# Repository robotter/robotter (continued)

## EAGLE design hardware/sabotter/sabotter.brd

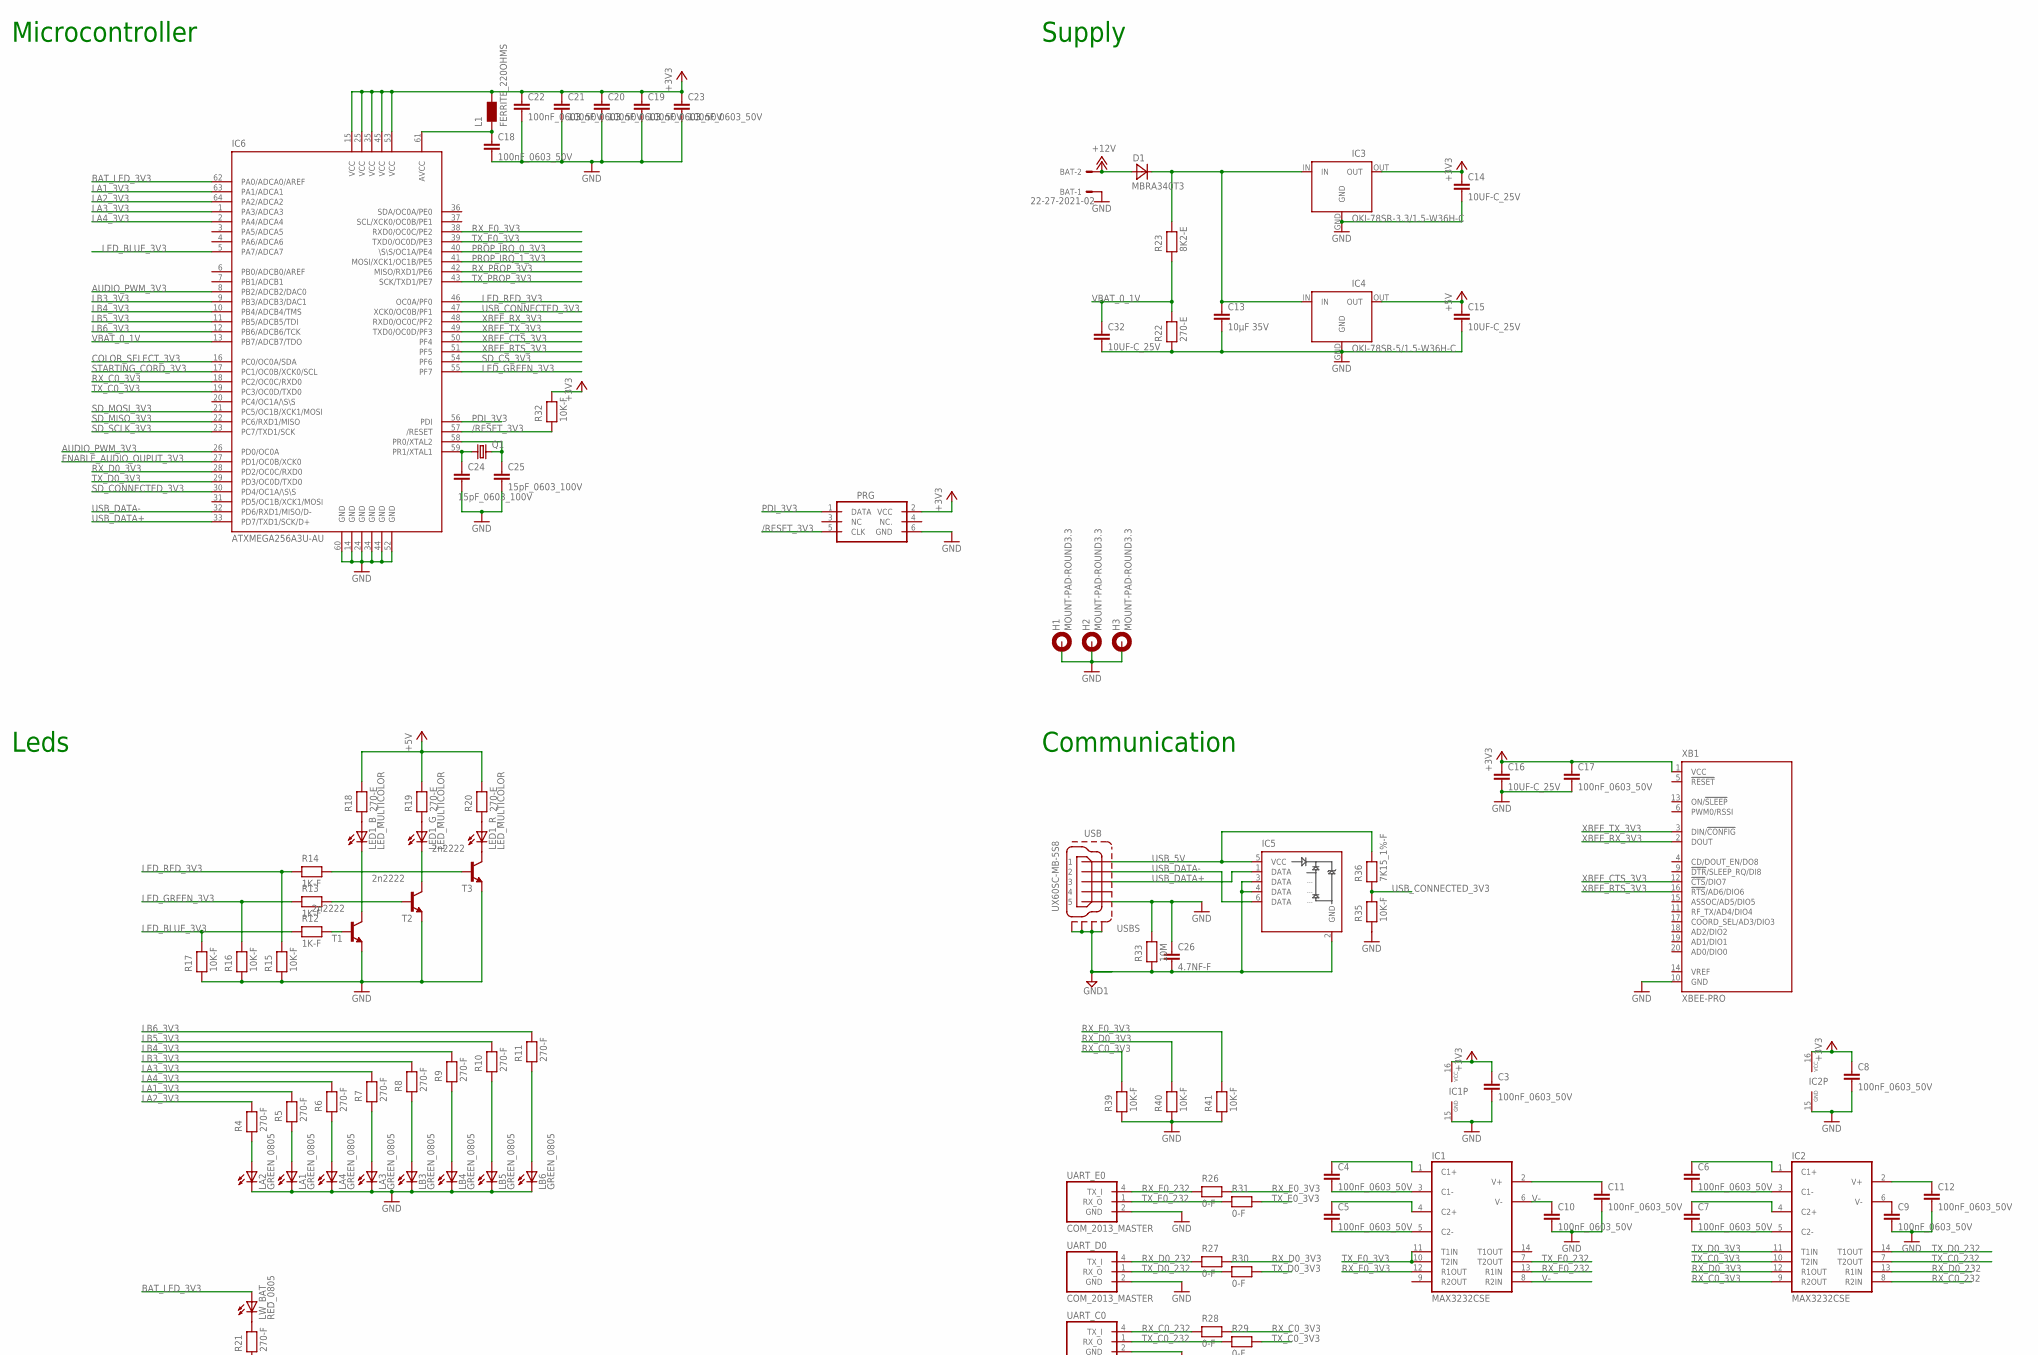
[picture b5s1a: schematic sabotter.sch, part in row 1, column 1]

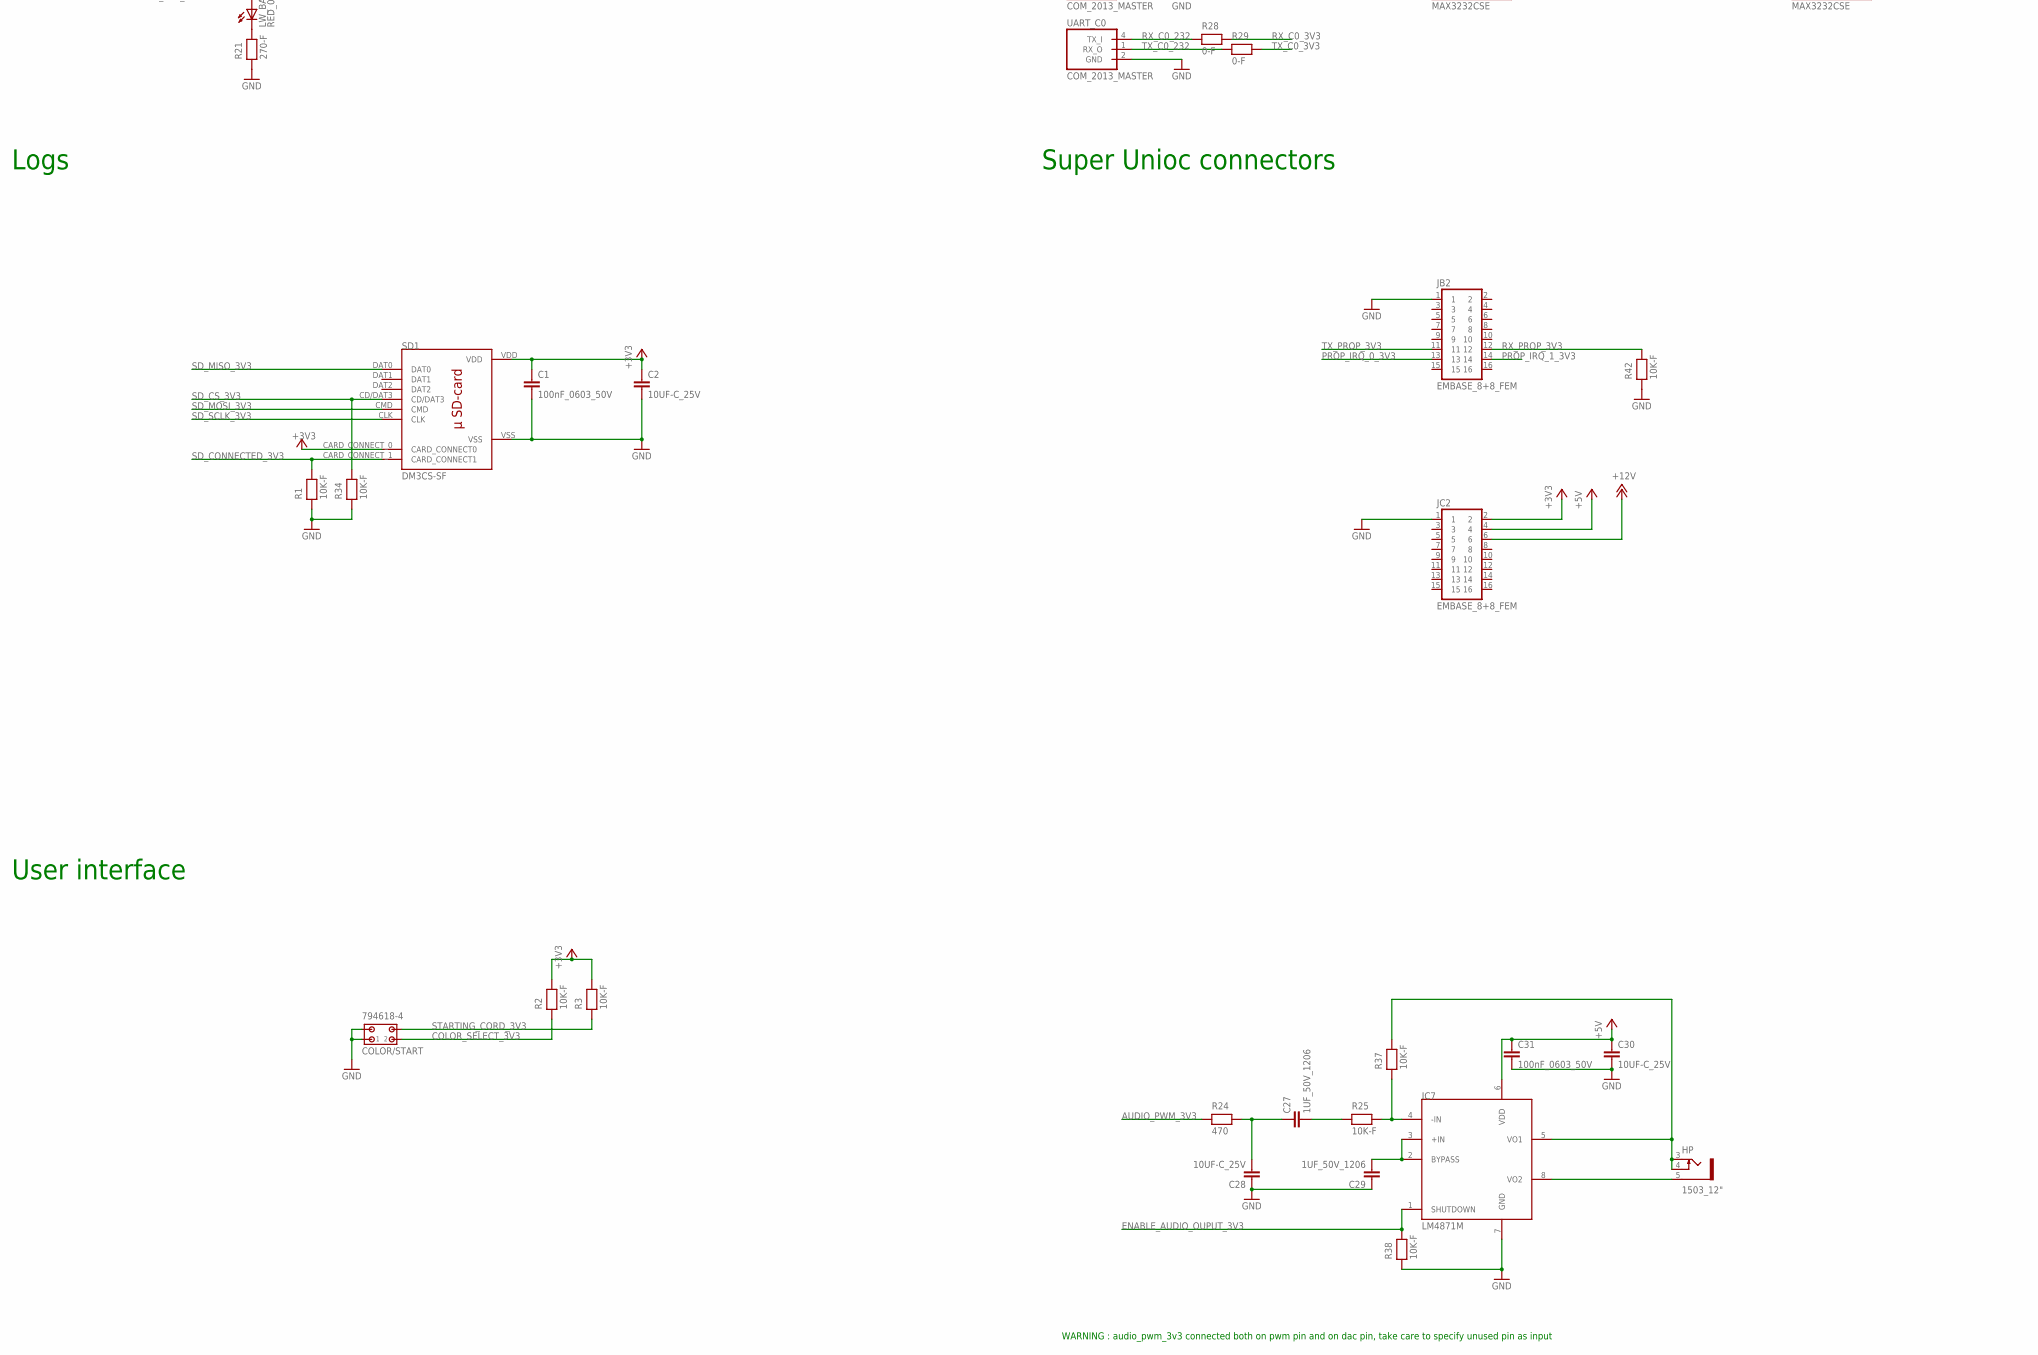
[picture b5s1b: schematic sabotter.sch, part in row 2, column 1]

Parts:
BAT: 22-27-2021-02; 6410-02
C1, C3, C4, C5, C6, C7, C8, C9, C10, C11, C12, C17, C18, C19, C20, C21, C22, C23, C31: 100nF_0603_50V; C0603
C2, C14, C15, C16, C28, C30, C32: 10UF-C_25V; C1210
C13: 10µF 35V; C1210
C24, C25: 15pF_0603_100V; C0603
C26: 4.7NF-F; C0603
C27, C29: 1UF_50V_1206; C1206
COLOR/START: 794618-4
D1: MBRA340T3; SMA
H1, H2, H3: MOUNT-PAD-ROUND3.3; 3,3-PAD
HP: 1503_12"; 1503_12
IC1, IC2: MAX3232CSE; SO16
IC3: OKI-78SR-3.3/1.5-W36H-C; OKI78SR-HORIZONTAL
IC4: OKI-78SR-5/1.5-W36H-C; OKI78SR-HORIZONTAL
IC5: LXES2SBAA4-016; LXES2BAA4
IC6: ATXMEGA256A3U-AU; TQFP64
IC7: LM4871M; SO8
JB2: EMBASE_8+8_FEM
JC2: EMBASE_8+8_FEM
L1: FERRITE_220OHMS; R0603
LA1, LA2, LA3, LA4: GREEN_0805; CHIP-LED0805
LB3, LB4, LB5, LB6: GREEN_0805; CHIP-LED0805
LED1: LED_MULTICOLOR; PLCC6
LW_BAT: RED_0805; CHIP-LED0805
PRG: PDI_ATMELL; ML6L
Q1: CRYSTAL_16MHZ_HC49UP; HC49UP
R1, R2, R3, R15, R16, R17, R25, R32, R34, R35, R37, R38, R39, R40, R41, R42: 10K-F; R0603
R4, R5, R6, R7, R8, R9, R10, R11, R21: 270-F; R0603
R12, R13, R14: 1K-F; R0603
R18, R19, R20, R22: 270-E; R0805
R23: 8K2-E; R0805
R24: 470; R0603
R26, R27, R28, R29, R30, R31: 0-F; R0603
R33: 10M; R0603
R36: 7K15_1%-F; R0603
SD1: DM3CS-SF
T1, T2, T3: 2n2222; SOT23-BEC
UART_C0: COM_2013_MASTER; MICROMATCH-4_SMD
UART_D0: COM_2013_MASTER; MICROMATCH-4_SMD
UART_E0: COM_2013_MASTER; MICROMATCH-4_SMD
USB: UX60SC-MB-5S8; UX60-MB-5S8
XB1: XBEE-PRO

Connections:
+3V3: C1.1, C2.1, C3.1, C8.1, C14.1, C16.1, C17.1, C19.1, C20.1, C21.1, C22.1, C23.1, IC1.16 (VCC), IC2.16 (VCC), IC3.OUT, IC6.15 (VCC), IC6.25 (VCC), IC6.35 (VCC), IC6.45 (VCC), IC6.53 (VCC), JC2.2, L1.2, PRG.2 (VCC), R2.2, R3.2, R32.2, SD1.CARD_CONNECT_0 (CARD_CONNECT0), SD1.VDD, XB1.1 (VCC)
+5V: C15.1, C30.1, C31.1, IC4.OUT, IC7.6 (VDD), JC2.4, R18.2, R19.2, R20.2
+12V: BAT.2, D1.A, JC2.6
/RESET_3V3: IC6.57 (/RESET), PRG.5 (CLK), R32.1
AUDIO_PWM_3V3: IC6.8 (PB2/ADCB2/DAC0), IC6.26 (PD0/OC0A), R24.1
BAT_LED_3V3: IC6.62 (PA0/ADCA0/AREF), LW_BAT.A
COLOR_SELECT_3V3: COLOR/START.2, IC6.16 (PC0/OC0A/SDA), R2.1
ENABLE_AUDIO_OUPUT_3V3: IC6.27 (PD1/OC0B/XCK0), IC7.1 (SHUTDOWN), R38.2
GND: BAT.1, C1.2, C2.2, C3.2, C8.2, C9.2, C10.2, C11.2, C12.2, C13.2, C14.2, C15.2, C16.2, C17.2, C18.2, C19.2, C20.2, C21.2, C22.2, C23.2, C24.2, C25.2, C26.1, C28.1, C29.1, C30.2, C31.2, C32.2, COLOR/START.1, COLOR/START.3, H1.B3,3, H2.B3,3, H3.B3,3, IC1.15 (GND), IC2.15 (GND), IC3.GND, IC4.GND, IC6.14 (GND), IC6.24 (GND), IC6.34 (GND), IC6.44 (GND), IC6.52 (GND), IC6.60 (GND), IC7.7 (GND), JB2.1, JC2.1, LA1.C, LA2.C, LA3.C, LA4.C, LB3.C, LB4.C, LB5.C, LB6.C, PRG.6 (GND), R1.1, R15.1, R16.1, R17.1, R21.1, R22.1, R33.2, R34.1, R35.1, R38.1, R39.1, R40.1, R41.1, R42.1, SD1.VSS, T1.E, T2.E, T3.E, UART_C0.2 (GND), UART_D0.2 (GND), UART_E0.2 (GND), USB.5, XB1.10 (GND)
GND1: C26.2, IC5.2 (GND), IC5.3 (DATA), IC5.4 (DATA), R33.1, USB.M1 (S1), USB.M2 (S2), USB.M3 (S3), USB.M4 (S4)
LA1_3V3: IC6.63 (PA1/ADCA1), R5.2
LA2_3V3: IC6.64 (PA2/ADCA2), R4.2
LA3_3V3: IC6.1 (PA3/ADCA3), R7.2
LA4_3V3: IC6.2 (PA4/ADCA4), R6.2
LB3_3V3: IC6.9 (PB3/ADCB3/DAC1), R8.2
LB4_3V3: IC6.10 (PB4/ADCB4/TMS), R9.2
LB5_3V3: IC6.11 (PB5/ADCB5/TDI), R10.2
LB6_3V3: IC6.12 (PB6/ADCB6/TCK), R11.2
LED_BLUE_3V3: IC6.5 (PA7/ADCA7), R12.1, R17.2
LED_GREEN_3V3: IC6.55 (PF7), R13.1, R16.2
LED_RED_3V3: IC6.46 (OC0A/PF0), R14.1, R15.2
unnamed: LA2.A, R4.1
unnamed: LA1.A, R5.1
unnamed: LB3.A, R8.1
unnamed: LA3.A, R7.1
unnamed: LB4.A, R9.1
unnamed: LB5.A, R10.1
unnamed: LB6.A, R11.1
unnamed: LA4.A, R6.1
unnamed: HP.5, IC7.8 (VO2)
unnamed: C29.2, IC7.2 (BYPASS), IC7.3 (+IN)
unnamed: C9.1, IC2.6 (V-)
unnamed: C27.1, C28.2, R24.2
unnamed: LED1.3 (C), T3.C
unnamed: LED1.2 (C), T2.C
unnamed: LED1.1 (C), T1.C
unnamed: C12.1, IC2.2 (V+)
unnamed: C11.1, IC1.2 (V+)
unnamed: R14.2, T3.B
unnamed: C4.1, IC1.1 (C1+)
unnamed: C6.1, IC2.1 (C1+)
unnamed: C5.1, IC1.4 (C2+)
unnamed: C5.2, IC1.5 (C2-)
unnamed: C4.2, IC1.3 (C1-)
unnamed: C6.2, IC2.3 (C1-)
unnamed: C7.1, IC2.4 (C2+)
unnamed: C7.2, IC2.5 (C2-)
unnamed: C27.2, R25.1
unnamed: IC7.4 (-IN), R25.2, R37.1
unnamed: HP.3, HP.4, IC7.5 (VO1), R37.2
unnamed: R13.2, T2.B
unnamed: R12.2, T1.B
unnamed: LED1.6 (A), R18.1
unnamed: LED1.5 (A), R19.1
unnamed: LED1.4 (A), R20.1
unnamed: LW_BAT.C, R21.2
unnamed: C13.1, D1.C, IC3.IN, IC4.IN, R23.2
unnamed: C18.1, IC6.61 (AVCC), L1.1
unnamed: C24.1, IC6.59 (PR1/XTAL1), Q1.1
unnamed: C25.1, IC6.58 (PR0/XTAL2), Q1.2
PDI_3V3: IC6.56 (PDI), PRG.1 (DATA)
PROP_IRQ_0_3V3: IC6.40 (\S\S/OC1A/PE4), JB2.13
PROP_IRQ_1_3V3: IC6.41 (MOSI/XCK1/OC1B/PE5), JB2.14
RX_C0_3V3: IC2.9 (R2OUT), IC6.18 (PC2/OC0C/RXD0), R28.2, R39.2
RX_C0_232: IC2.8 (R2IN), R28.1, UART_C0.4 (TX_I)
RX_D0_3V3: IC2.12 (R1OUT), IC6.28 (PD2/OC0C/RXD0), R27.2, R40.2
RX_D0_232: IC2.13 (R1IN), R27.1, UART_D0.4 (TX_I)
RX_E0_3V3: IC1.12 (R1OUT), IC6.38 (RXD0/OC0C/PE2), R26.2, R41.2
RX_E0_232: IC1.13 (R1IN), R26.1, UART_E0.4 (TX_I)
RX_PROP_3V3: IC6.42 (MISO/RXD1/PE6), JB2.12, R42.2
SD_CONNECTED_3V3: IC6.30 (PD4/OC1A/\S\S), R1.2, SD1.CARD_CONNECT_1 (CARD_CONNECT1)
SD_CS_3V3: IC6.54 (PF6), R34.2, SD1.CD/DAT3
SD_MISO_3V3: IC6.22 (PC6/RXD1/MISO), SD1.DAT0
SD_MOSI_3V3: IC6.21 (PC5/OC1B/XCK1/MOSI), SD1.CMD
SD_SCLK_3V3: IC6.23 (PC7/TXD1/SCK), SD1.CLK
STARTING_CORD_3V3: COLOR/START.4, IC6.17 (PC1/OC0B/XCK0/SCL), R3.1
TX_C0_3V3: IC2.10 (T2IN), IC6.19 (PC3/OC0D/TXD0), R29.2
TX_C0_232: IC2.7 (T2OUT), R29.1, UART_C0.1 (RX_O)
TX_D0_3V3: IC2.11 (T1IN), IC6.29 (PD3/OC0D/TXD0), R30.2
TX_D0_232: IC2.14 (T1OUT), R30.1, UART_D0.1 (RX_O)
TX_E0_3V3: IC1.10 (T2IN), IC1.11 (T1IN), IC6.39 (TXD0/OC0D/PE3), R31.2
TX_E0_232: IC1.7 (T2OUT), R31.1, UART_E0.1 (RX_O)
TX_PROP_3V3: IC6.43 (SCK/TXD1/PE7), JB2.11
USB_5V: IC5.5 (VCC), R36.2, USB.1
USB_CONNECTED_3V3: IC6.47 (XCK0/OC0B/PF1), R35.2, R36.1
USB_DATA+: IC5.1 (DATA), IC6.33 (PD7/TXD1/SCK/D+), USB.3
USB_DATA-: IC5.6 (DATA), IC6.32 (PD6/RXD1/MISO/D-), USB.2
V-: C10.1, IC1.6 (V-), IC1.8 (R2IN)
VBAT_0_1V: C32.1, IC6.13 (PB7/ADCB7/TDO), R22.2, R23.1
XBEE_CTS_3V3: IC6.50 (PF4), XB1.12 (!CTS!/DIO7)
XBEE_RTS_3V3: IC6.51 (PF5), XB1.16 (!RTS!/AD6/DIO6)
XBEE_RX_3V3: IC6.48 (RXD0/OC0C/PF2), XB1.2 (DOUT)
XBEE_TX_3V3: IC6.49 (TXD0/OC0D/PF3), XB1.3 (DIN/!CONFIG)

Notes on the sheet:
Microcontroller
Supply
Leds
Communication
Logs
Super Unioc connectors
User interface
WARNING : audio_pwm_3v3 connected both on pwm pin and on dac pin, take care to specify unused pin as input

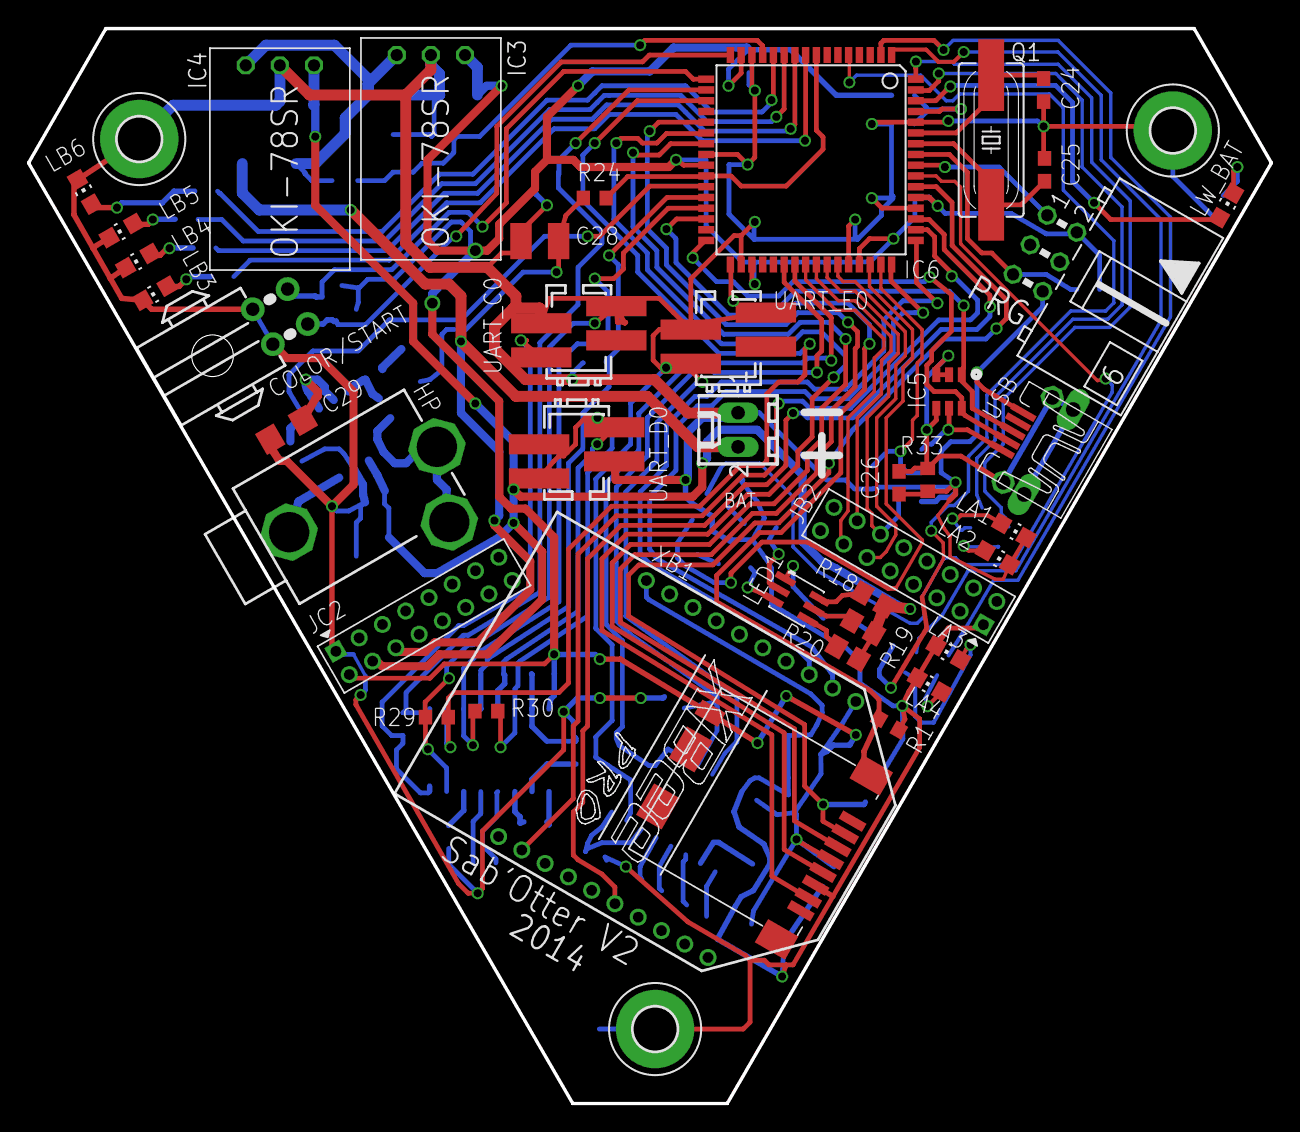
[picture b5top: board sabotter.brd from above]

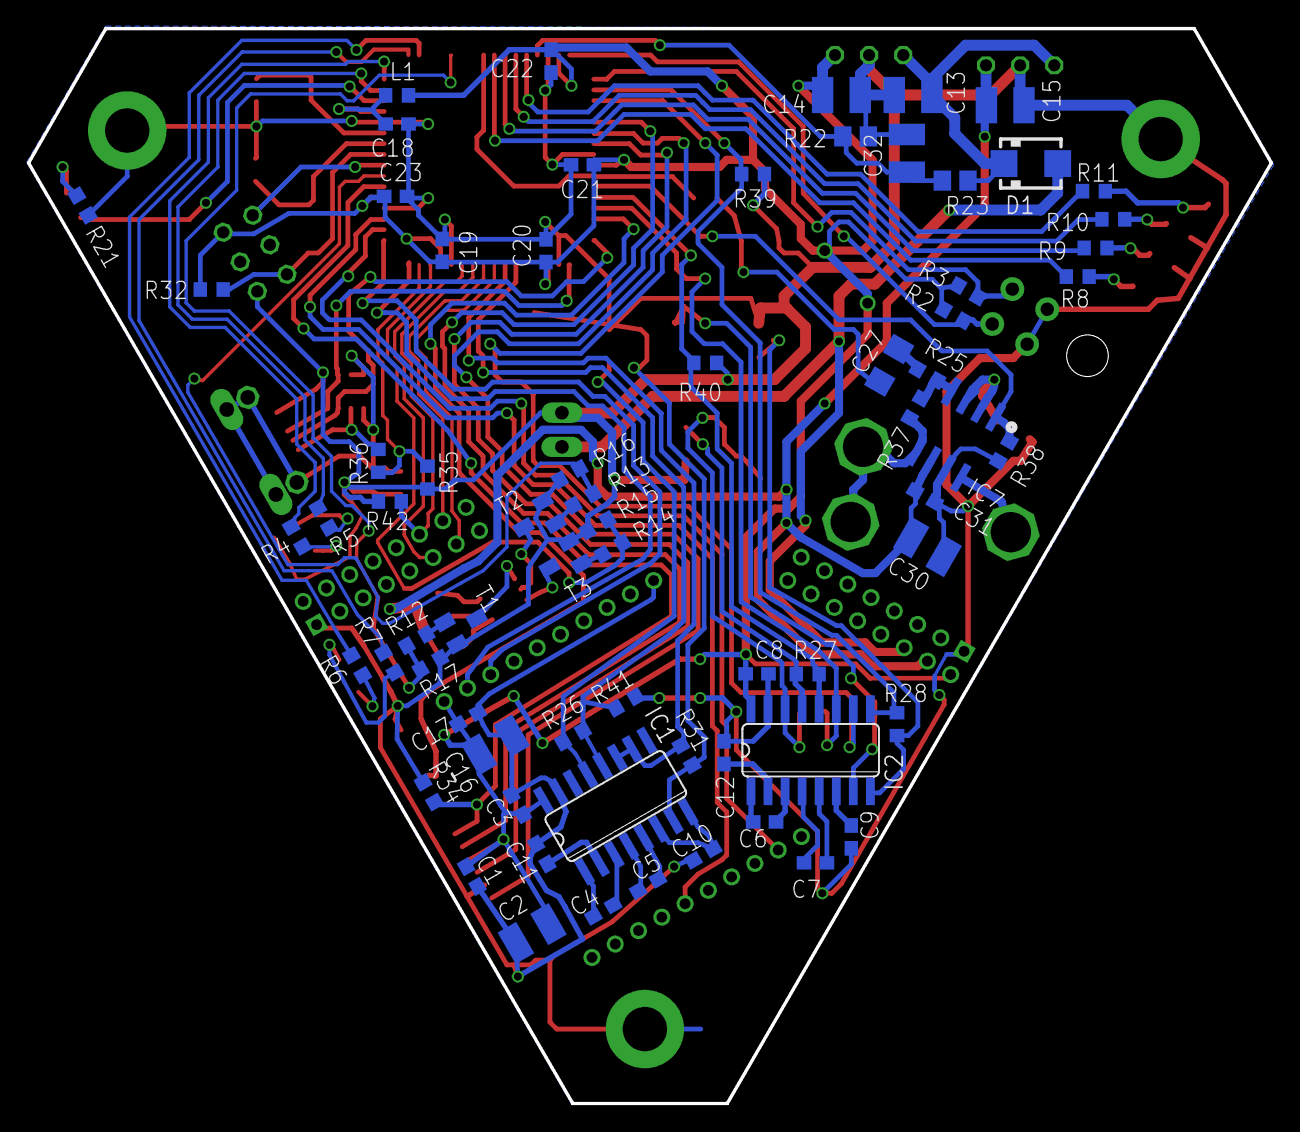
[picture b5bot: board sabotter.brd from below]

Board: 2 copper layers, 92.5 x 80.0 mm, 112 parts (69 on the bottom side), 93 nets.

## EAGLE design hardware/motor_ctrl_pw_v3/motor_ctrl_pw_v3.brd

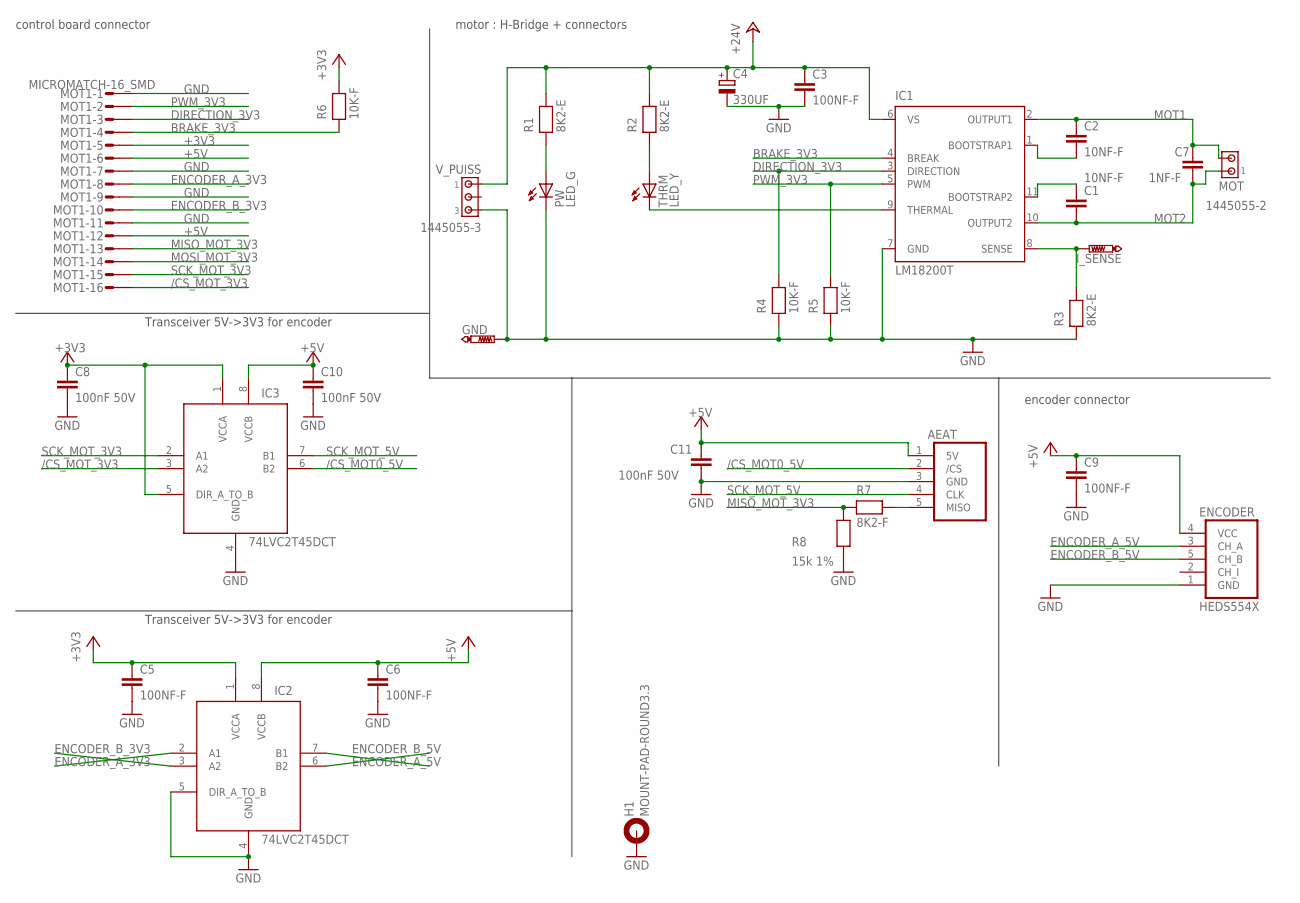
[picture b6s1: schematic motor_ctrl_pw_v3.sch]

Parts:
AEAT: AEAT-601X; 53047-05
C1, C2: 10NF-F; C0603
C3, C5, C6, C9: 100NF-F; C0603
C4: 330UF; PANASONIC_G
C7: 1NF-F; C0603
C8, C10, C11: 100nF 50V; C0603
ENCODER: HEDS554X; 22-05-1052
GND: PTR1PAD1-13; P1-13
H1: MOUNT-PAD-ROUND3.3; 3,3-PAD
IC1: LM18200T; TO-220-11
IC2, IC3: 74LVC2T45DCT; SSOP8
I_SENSE: PTR1PAD1-13; P1-13
MOT: 1445055-2
MOT1: MICROMATCH-16_SMD
PW: LED_G; CHIP-LED0805
R1, R2, R3: 8K2-E; R0805
R4, R5, R6: 10K-F; R0603
R7: 8K2-F; R0603
R8: 15k 1%; R0603
THRM: LED_Y; CHIP-LED0805
V_PUISS: 1445055-3

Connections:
+3V3: C5.1, C8.1, IC2.1 (VCCA), IC3.1 (VCCA), IC3.5 (DIR_A_TO_B), MOT1.5, R6.2
+5V: AEAT.1 (5V), C6.1, C9.1, C10.1, C11.1, ENCODER.4 (VCC), IC2.8 (VCCB), IC3.8 (VCCB), MOT1.6, MOT1.12
+24V: C3.1, C4.+, IC1.6 (VS), R1.2, R2.2, V_PUISS.1
/CS_MOT0_5V: AEAT.2 (/CS), IC3.6 (B2)
/CS_MOT_3V3: IC3.3 (A2), MOT1.16
BRAKE_3V3: IC1.4 (BREAK), MOT1.4, R6.1
DIRECTION_3V3: IC1.3 (DIRECTION), MOT1.3, R4.2
ENCODER_A_3V3: IC2.2 (A1), MOT1.8
ENCODER_A_5V: ENCODER.3 (CH_A), IC2.7 (B1)
ENCODER_B_3V3: IC2.3 (A2), MOT1.10
ENCODER_B_5V: ENCODER.5 (CH_B), IC2.6 (B2)
GND: AEAT.3 (GND), C3.2, C4.-, C5.2, C6.2, C8.2, C9.2, C10.2, C11.2, ENCODER.1 (GND), GND.TP, H1.B3,3, IC1.7 (GND), IC2.4 (GND), IC2.5 (DIR_A_TO_B), IC3.4 (GND), MOT1.1, MOT1.7, MOT1.9, MOT1.11, PW.C, R3.1, R4.1, R5.1, R8.1, V_PUISS.3
MISO_MOT_3V3: MOT1.13, R7.1, R8.2
MOSI_MOT_3V3: MOT1.14
MOT1: C2.1, C7.1, IC1.2 (OUTPUT1), MOT.2
MOT2: C1.2, C7.2, IC1.10 (OUTPUT2), MOT.1
unnamed: R2.1, THRM.A
unnamed: IC1.8 (SENSE), I_SENSE.TP, R3.2
unnamed: PW.A, R1.1
unnamed: IC1.9 (THERMAL), THRM.C
unnamed: C2.2, IC1.1 (BOOTSTRAP1)
unnamed: C1.1, IC1.11 (BOOTSTRAP2)
unnamed: AEAT.5 (MISO), R7.2
PWM_3V3: IC1.5 (PWM), MOT1.2, R5.2
SCK_MOT_3V3: IC3.2 (A1), MOT1.15
SCK_MOT_5V: AEAT.4 (CLK), IC3.7 (B1)

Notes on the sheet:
control board connector
motor : H-Bridge + connectors
Transceiver 5V->3V3 for encoder
encoder connector

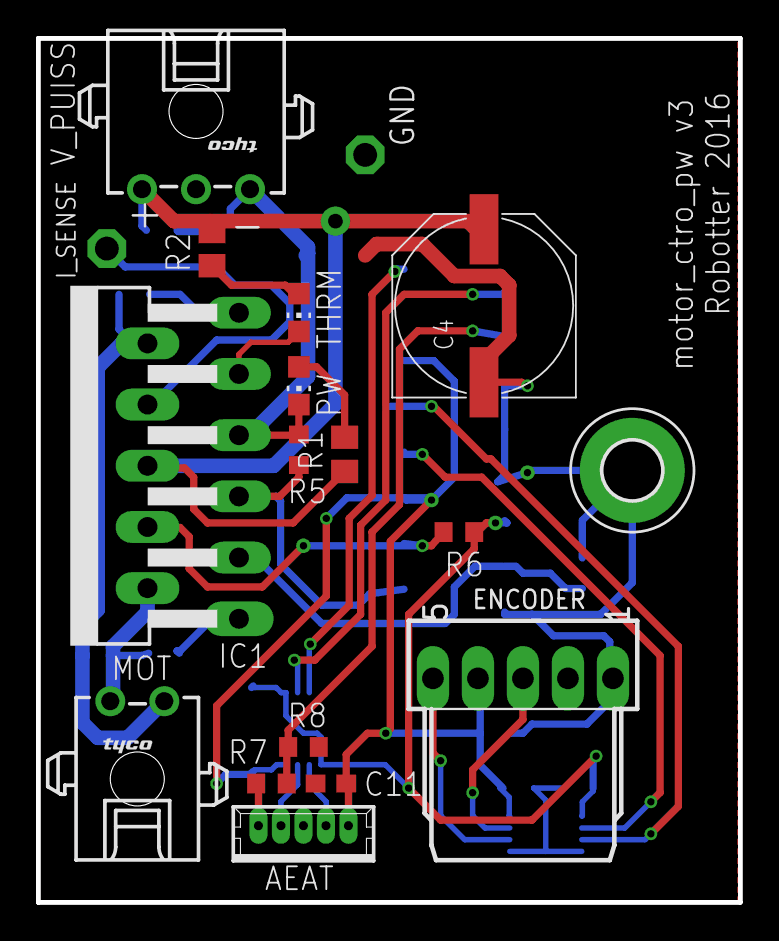
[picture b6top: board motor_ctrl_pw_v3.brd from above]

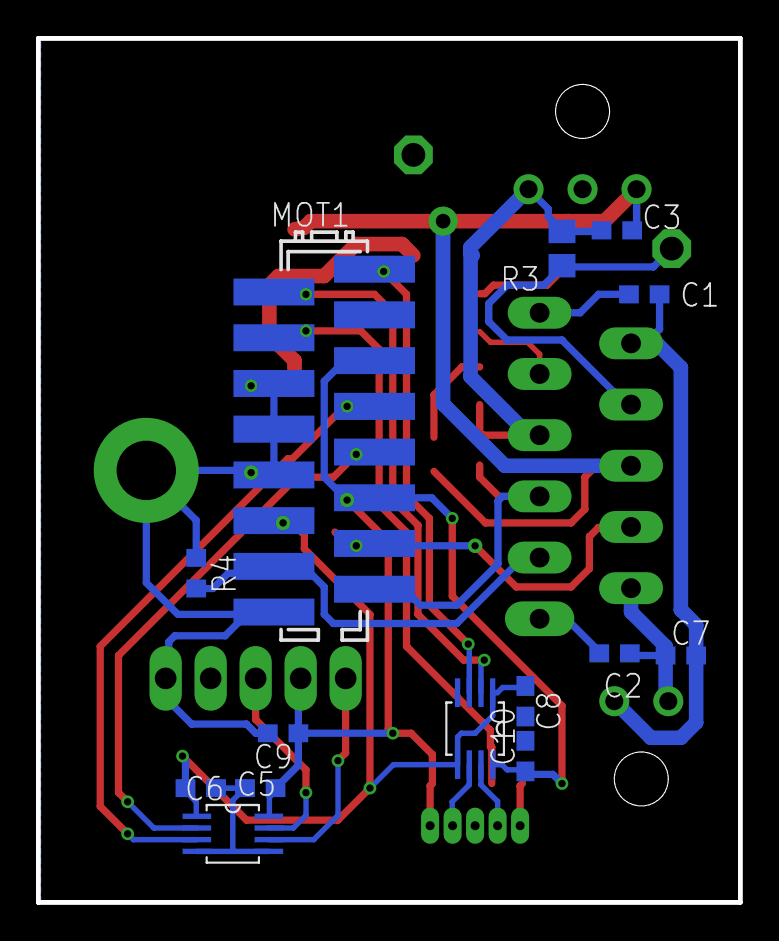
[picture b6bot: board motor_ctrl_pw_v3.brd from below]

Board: 2 copper layers, 39.0 x 48.0 mm, 32 parts (14 on the bottom side), 25 nets.

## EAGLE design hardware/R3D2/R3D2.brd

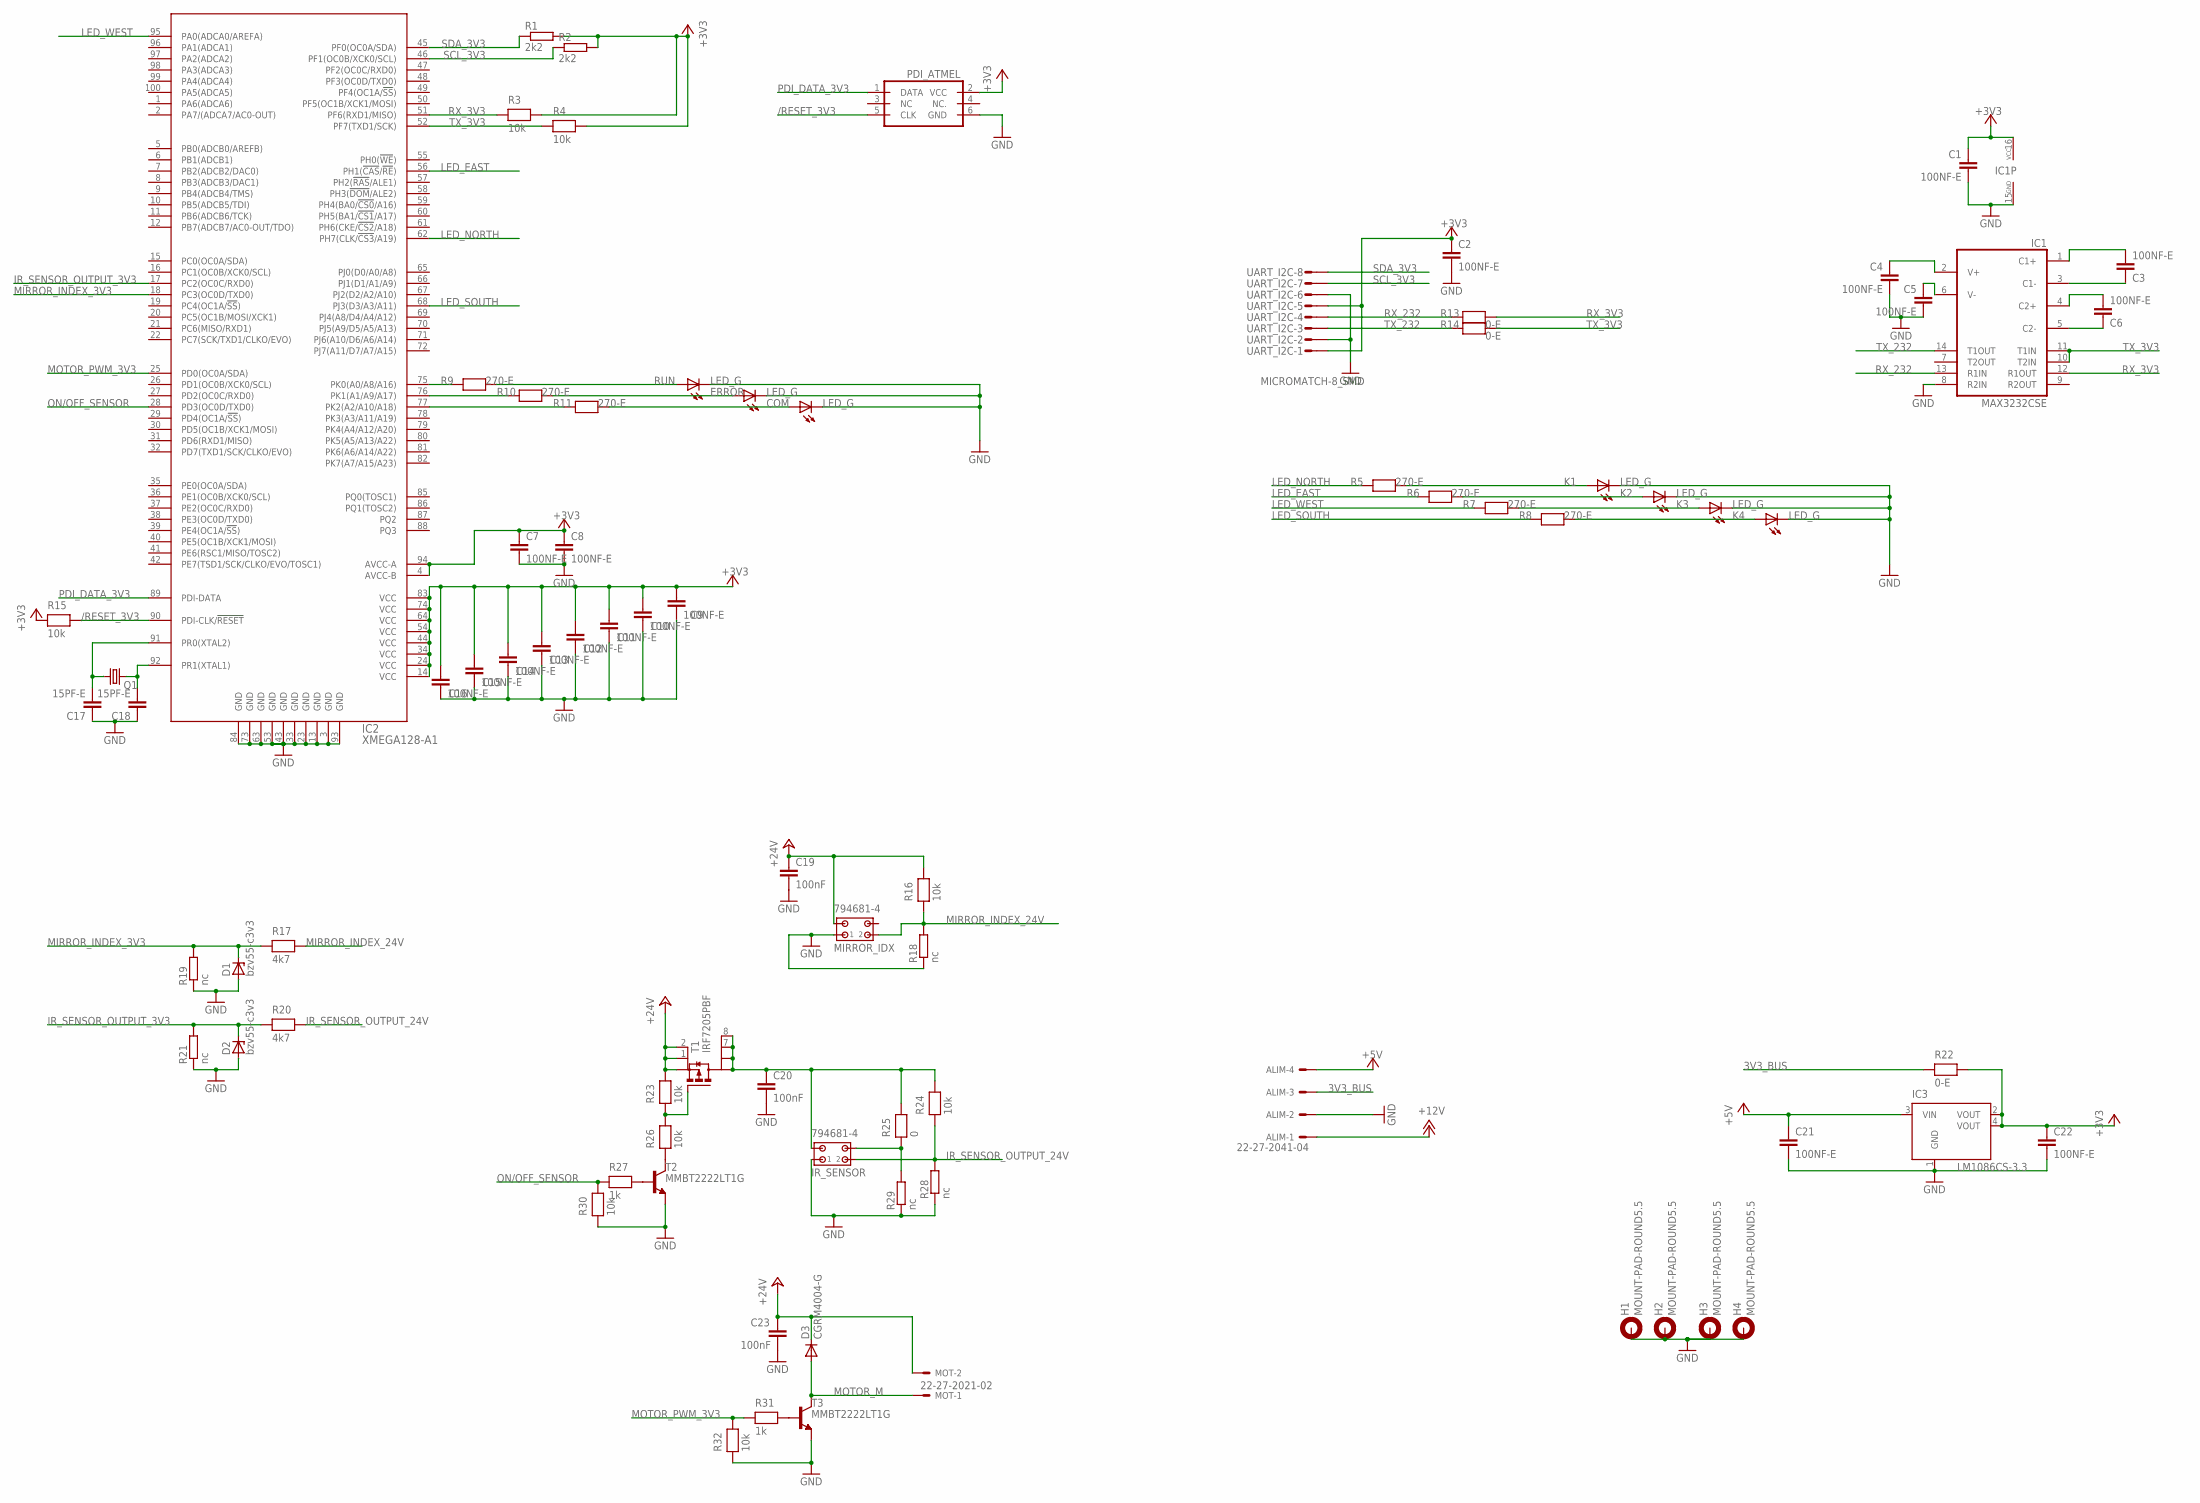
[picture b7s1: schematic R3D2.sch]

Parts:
ALIM: 22-27-2041-04; 6410-04
C1, C2, C3, C4, C5, C6, C7, C8, C9, C10, C11, C12, C13, C14, C15, C16, C21, C22: 100NF-E; C0805
C17, C18: 15PF-E; C0805
C19, C23: 100nF; C0805
C20: 100nF; C0603
COM: LED_G; CHIP-LED0805
D1, D2: bzv55-c3v3; SOD80C
D3: CGRM4004-G; SOD-123_MINI-SMA
ERROR: LED_G; CHIP-LED0805
H1, H2, H3, H4: MOUNT-PAD-ROUND5.5; 5,5-PAD
IC1: MAX3232CSE; SO16
IC2: XMEGA128-A1; TQFP100
IC3: LM1086CS-3.3; TO263
IR_SENSOR: 794681-4
K1, K2, K3, K4: LED_G; CHIP-LED0805
MIRROR_IDX: 794681-4
MOT: 22-27-2021-02; 6410-02
PDI_ATMEL: PDI_ATMEL; ML6
Q1: CRYSTAL_16MHZ_HC49UP; HC49UP
R1, R2: 2k2; R0603
R3, R4, R15, R16, R23, R24, R26, R30, R32: 10k; R0603
R5, R6, R7, R8, R9, R10, R11: 270-E; R0805
R13, R14, R22: 0-E; R0805
R17, R20: 4k7; R0805
R18: nc; R0805
R19, R21, R28, R29: nc; R0603
R25: 0; R0603
R27, R31: 1k; R0603
RUN: LED_G; CHIP-LED0805
T1: IRF7205PBF; SO8
T2, T3: MMBT2222LT1G; SOT23-BEC
UART_I2C: MICROMATCH-8_SMD

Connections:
3V3_BUS: ALIM.3, R22.1
+3V3: C1.1, C2.1, C7.1, C8.1, C9.1, C10.1, C11.1, C12.1, C13.1, C14.1, C15.1, C16.1, C22.1, IC1.16 (VCC), IC2.4 (AVCC-B), IC2.14 (VCC), IC2.24 (VCC), IC2.34 (VCC), IC2.44 (VCC), IC2.54 (VCC), IC2.64 (VCC), IC2.74 (VCC), IC2.83 (VCC), IC2.94 (AVCC-A), IC3.2 (VOUT), IC3.4 (VOUT), PDI_ATMEL.2 (VCC), R1.2, R2.2, R3.2, R4.2, R15.1, R22.2, UART_I2C.1, UART_I2C.5
+5V: ALIM.4, C21.1, IC3.3 (VIN)
+12V: ALIM.1
+24V: C19.1, C23.1, D3.C, MIRROR_IDX.3, MOT.2, R16.2, R23.2, T1.1 (S), T1.2 (S), T1.3 (S)
/RESET_3V3: IC2.90 (PDI-CLK/!RESET), PDI_ATMEL.5 (CLK), R15.2
GND: ALIM.2, C1.2, C2.2, C4.2, C5.2, C7.2, C8.2, C9.2, C10.2, C11.2, C12.2, C13.2, C14.2, C15.2, C16.2, C17.1, C18.1, C19.2, C20.2, C21.2, C22.2, C23.2, COM.C, D1.A, D2.A, ERROR.C, H1.B5,5, H2.B5,5, H3.B5,5, H4.B5,5, IC1.8 (R2IN), IC1.15 (GND), IC2.3 (GND), IC2.13 (GND), IC2.23 (GND), IC2.33 (GND), IC2.43 (GND), IC2.53 (GND), IC2.63 (GND), IC2.73 (GND), IC2.84 (GND), IC2.93 (GND), IC3.1 (GND), IR_SENSOR.1, K1.C, K2.C, K3.C, K4.C, MIRROR_IDX.1, PDI_ATMEL.6 (GND), R18.1, R19.1, R21.1, R28.1, R29.1, R30.1, R32.1, RUN.C, T2.E, T3.E, UART_I2C.2, UART_I2C.6
IR_SENSOR_OUTPUT_3V3: D2.C, IC2.17 (PC2(OC0C/RXD0)), R20.1, R21.2
IR_SENSOR_OUTPUT_24V: IR_SENSOR.2, R20.2, R24.1, R28.2
LED_EAST: IC2.56 (PH1(!CAS!/!RE!)), R6.1
LED_NORTH: IC2.62 (PH7(CLK/!CS3!/A19)), R5.1
LED_SOUTH: IC2.68 (PJ3(D3/A3/A11)), R8.1
LED_WEST: IC2.95 (PA0(ADCA0/AREFA)), R7.1
MIRROR_INDEX_3V3: D1.C, IC2.18 (PC3(OC0D/TXD0)), R17.1, R19.2
MIRROR_INDEX_24V: MIRROR_IDX.2, R16.1, R17.2, R18.2
MOTOR_M: D3.A, MOT.1, T3.C
MOTOR_PWM_3V3: IC2.25 (PD0(OC0A/SDA)), R31.1, R32.2
unnamed: C3.1, IC1.1 (C1+)
unnamed: R9.2, RUN.A
unnamed: R31.2, T3.B
unnamed: ERROR.A, R10.2
unnamed: C3.2, IC1.3 (C1-)
unnamed: C6.1, IC1.4 (C2+)
unnamed: COM.A, R11.2
unnamed: IC2.75 (PK0(A0/A8/A16)), R9.1
unnamed: IC2.76 (PK1(A1/A9/A17)), R10.1
unnamed: C4.1, IC1.2 (V+)
unnamed: IC2.77 (PK2(A2/A10/A18)), R11.1
unnamed: C5.1, IC1.6 (V-)
unnamed: C6.2, IC1.5 (C2-)
unnamed: C17.2, IC2.91 (PR0(XTAL2)), Q1.1
unnamed: C18.2, IC2.92 (PR1(XTAL1)), Q1.2
unnamed: K1.A, R5.2
unnamed: K2.A, R6.2
unnamed: K3.A, R7.2
unnamed: K4.A, R8.2
unnamed: R27.2, T2.B
unnamed: C20.1, IR_SENSOR.3, R24.2, R25.2, T1.5 (D), T1.6 (D), T1.7 (D), T1.8 (D)
unnamed: R26.1, T2.C
unnamed: R23.1, R26.2, T1.4 (G)
unnamed: IR_SENSOR.4, R25.1, R29.2
ON/OFF_SENSOR: IC2.28 (PD3(OC0D/TXD0)), R27.1, R30.2
PDI_DATA_3V3: IC2.89 (PDI-DATA), PDI_ATMEL.1 (DATA)
RX_3V3: IC1.12 (R1OUT), IC2.51 (PF6(RXD1/MISO)), R3.1, R13.2
RX_232: IC1.13 (R1IN), R13.1, UART_I2C.4
SCL_3V3: IC2.46 (PF1(OC0B/XCK0/SCL)), R2.1, UART_I2C.7
SDA_3V3: IC2.45 (PF0(OC0A/SDA)), R1.1, UART_I2C.8
TX_3V3: IC1.10 (T2IN), IC1.11 (T1IN), IC2.52 (PF7(TXD1/SCK)), R4.1, R14.2
TX_232: IC1.14 (T1OUT), R14.1, UART_I2C.3
